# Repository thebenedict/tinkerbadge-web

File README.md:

# Tinker Badge Web Viewer

A static KiCad project viewer with an interactive 3D assembly, searchable schematics, PCB layers, and source documentation. Project metadata and native CAD exports drive the pages. Tinker Badge is the current integration target; Harvest remains a separate regression example.

## Run locally

Requires Node 18+ and Python 3. CAD exports use KiCad 10.0.8.

```sh
npm ci
npm run build
npm run preview
```

Open **http://127.0.0.1:4173**. The preview serves `dist/` on loopback. Use HTTP rather than opening HTML through `file://`.

The included `public/data/` snapshot can rebuild the interface without KiCad. Its manifest identifies the actual project and snapshot. `npm run dev` builds and starts the preview. After editing files, rebuild and refresh the browser.

## Export a project

```sh
npm run export:badge
npm run check
```

For Harvest:

```sh
npm run export:harvest
npm run check
```

For another configuration or source location:

```sh
python3 scripts/export_assets.py \
  --config config/badge.json \
  --source ../tinkerbadge-hardware \
  --kicad-cli /Applications/KiCad/KiCad.app/Contents/MacOS/kicad-cli
```

The exporter copies allowlisted native files, local libraries, and referenced models into a private working directory. It runs KiCad against those copies, checks source and dependency hashes again, and promotes the new manifest only after the export completes. Native downloads retain the original source bytes. Logs stay in `.work/`.

Export from a consistent CAD checkpoint. If a sheet, footprint, model, document, or dependency changes during export, the snapshot is rejected. The badge configuration also pins the approved board hash; update that pin only after reviewing a new hardware checkpoint. Before export, run the hardware repository’s `tools/refresh_publication.py` and commit the resulting snapshot. The web exporter verifies that its selected source files match one hardware commit, and that the manufacturing, electrical and enclosure evidence all match those files. It reads the hardware project without modifying it.

## Project metadata

`config/badge.json` and `config/harvest.json` use schema version 2. A project configuration names:

- The source directory, relative to this viewer project unless overridden with `--source`.
- The project name, description, revision, status, and maintained README.
- Explicit variant IDs and paths to the root schematic, PCB, and KiCad project.
- The native instance project name used by hierarchical schematics.
- Documents and CAD directories to include in the source bundle.
- Optional facts, named assembly accessories, and source-backed component-name inputs.

The schematic and PCB inputs are independent. A schematic-only project gets a schematic preview and no PCB tab. A board with an outline can have a 3D view before placement. Missing model geometry leaves the schematic, PCB layers, and available component metadata usable.

To adapt another KiCad project, add a configuration with its real filenames and metadata, export it, run the checks, and review the resulting pages. The current adapter targets KiCad 10's native file and export structures. Unfamiliar hierarchy or model conventions need validation and tests before release.

Interface copy lives in `config/presentation.json` and applies only to its matching `projectName`. It can override the landing product line, supply brief example interactions, and omit named README sections from the landing page. The full source README, its document page, and the native download remain unchanged.

## Views

- **Overview:** maintained README, source documents, assembly poster, optional interactive model, and downloads.
- **Schematic:** pan, zoom, fit, hierarchical sheet selection, project-wide name/reference/value search, source properties, and PDF/SVG/native downloads.
- **PCB:** all exported copper layers, fabrication and mask layers, mirrored back view, front/back presets, and name/reference/value/net search.

Each variant and view has a static URL. Sheet links use the full native sheet-instance identity. Searching for a component on another sheet opens that sheet and focuses its symbol. A component's 3D details link to the matching PCB reference and schematic sheet.

The model runtime, GLB, and component index load after **Explore in 3D**. Schematic and PCB drawings load on their own pages. All viewer assets use the same origin; no backend is required.

## Components and assembly accessories

Click a component to highlight it and read its descriptive name, reference, value, part number, supplier code, footprint, BOM inclusion, quantity, and nets. Datasheet links come from the source. The reference selector provides the same details without precise pointing. Parts without a separate model remain selectable in the list.

**Focus** moves the camera toward the selected model. **Clear** or Escape removes the selection. Dragging and multi-pointer gestures do not select a component. Visible PCB and accessory geometry blocks picking through it.

The badge's **Show display and battery** checkbox controls separate assembly objects. It starts off in 3D; enable it to show the source-derived assembly geometry. An explicit choice is retained for that model in the current tab, including retries and browser Back navigation. The display is a source-derived glass envelope with a proposed 4.5 mm underside clearance. The battery is a 35 × 55 × 7 mm size allowance; the pack, cable, and mounting are still open. These objects are excluded from the electrical BOM.

Accessory metadata names an exact native board-only footprint and source model. When KiCad omits the review WRL from GLB, the exporter can reconstruct its verified cuboids and calibrate placement against native component transforms on both board sides. Unsupported geometry or inconsistent anchors disables that fallback. The interactive viewer does not invent mounting hardware, cables, or flex routing.

## Identity and provenance

Each PCB record keeps its footprint UUID and native schematic instance path. The exporter resolves a root-relative path only against the known schematic root, then checks the reference. It compares values, footprints, BOM fields, and assembly flags. Unplaced symbols and board-only items remain explicit; conflicting properties are reported and details use the PCB values.

The GLB binder verifies KiCad's reference-named assembly parents and adds variant-qualified UUIDs in node extras. `components.json` records source hashes, model hash, metadata, and exact mesh ownership. Ambiguous identities stop binding. Missing bodies are recorded as missing rather than assigned to a nearby part.

For reviewed routing checkpoints, optional `routingReview` inputs identify the checkpoint manifest, native DRC report, exact remaining endpoints, and review document. The exporter binds them to the board hash and validates report counts and endpoint agreement. Their source hashes accompany the PCB-only progress note; inconsistent reports stop export.

The browser validates the index before enabling inspection. Picking follows UUID ancestry from actual mesh hits. The model optimizer merges compatible primitives within each mesh and verifies triangle attributes, winding, materials, names, transforms, and bounds. The original native GLB is included as a download.

Readable names come from the planning BOM's Description tables, joined through reviewed reference-to-BOM contracts and exact current part numbers. A unique part-number match is allowed only when it identifies one current reference. Shared parts do not inherit another circuit's role. Standard resistor, capacitor, and inductor names can use their embedded native library descriptions. Missing or ambiguous names keep the native value instead.

The same `displayName` and `displayNameSource` fields reach the 3D index, verified PCB records, and schematic symbols. Source paths, hashes, table rows, and association evidence remain available for audit. Names are searchable in both drawing views.

BOM quantity is the populated count of the exact part in the selected board snapshot. Historical BOM CSVs, stock, and prices are not used.

## Controls

**3D:** drag to orbit. Focus the canvas before scrolling to zoom. Keyboard arrows rotate, +/− zoom, and Home resets. On touch screens, use two fingers to orbit and zoom. Rendering runs when the view changes and pauses in background tabs.

**2D:** drag to pan, scroll or pinch to zoom. Keyboard arrows pan, +/− zoom, and Home/0 fit. Search results focus symbol or footprint origins.

On the PCB, **Back** mirrors the viewing direction. **Back set** selects the rear layers. These controls are independent.

## Verify changes

```sh
npm run check
```

This runs unit tests, builds the static pages, checks local links and artifact hashes, validates hierarchy and component identities, probes real model triangles, and checks that PCB layers share a coordinate system. Browser checks and remaining coverage are recorded in `QA.md`.

For an isolated fixture, set `VIEWER_PUBLIC` and `VIEWER_DIST` to separate directories inside this project. `VIEWER_PUBLIC` contains `data/manifest.json`; `VIEWER_DIST` is the generated site. Build, check, and preview scripts honor these paths. `PORT` changes the loopback preview port.

Read `docs/style_guide/writing.md` before changing copy. Use descriptive labels and omit decorative numbering. Native sheet names and source documents retain their maintained text.

## Deployment

`dist/` is the complete static site and uses relative URLs for subpath hosting. Deploy it as a unit only after checking its manifest and project identity. Content-hashed scripts, styles, and immutable snapshot assets can be cached independently of entry pages.

See [publishing setup](docs/publishing.md) for release checks and deployment configuration. Review third-party model licenses before public redistribution.

## Current limits

- PCB revision 0.3 has zero open connections or error-severity ERC/DRC findings in the bound publication evidence. The enclosure is an A2 fit prototype; battery, display, RF and physical qualification remain open.
- Component selection marks real model bodies; 2D reference markers mark symbol or footprint origins. Live cross-highlighting between separate open views is future work.
- The maintained README is rendered from its source, with configured landing-page omissions. Links outside the snapshot allowlist appear as dotted text.
- Arbitrary STEP assemblies, unusual nested model exports, and unsupported accessory meshes need adapter work and tests.
- Physical-phone performance, sustained memory use, Safari, and Firefox still need testing.

## Files

- `config/`: explicit project metadata and source allowlists
- `src/`: browser modules and styles
- `scripts/export_assets.py`: frozen snapshots and native KiCad exports
- `scripts/kicad_source.py`: source parsing, hierarchy, models, and metadata
- `scripts/component_names.py`: BOM and native-description names with provenance
- `scripts/presentation.mjs`: landing-page README filtering
- `scripts/interactions.mjs`: static example-interaction lists with decorative sketches
- `scripts/bind_components.mjs`: component and accessory bindings
- `scripts/optimize_glb.mjs`: checked per-mesh primitive consolidation
- `scripts/build.mjs`: static pages and browser bundles
- `scripts/check.mjs`: artifact and integration checks
- `scripts/qa-serve.mjs`: local error and loading fixtures
- `tests/`: JavaScript and Python regression tests
- `public/data/`: immutable exports and active manifest
- `dist/`: generated static site
- `.work/`: copied inputs, export logs, and local fixtures

See `web_viewer.md` for the longer-term specification.

## Feature callouts

The badge front page starts with Front, Components, and Back KiCad renders and labeled hardware features. Desktop shows all leader lines. On phones, every label stays visible and selecting one shows its leader line. Keyboard users can select a view and move through the labels. The 3D model still loads only after **Explore in 3D**.

Feature copy and one representative reference per feature live in `config/features/badge.json`. Each label has a single leader. Anchors come from the snapshot’s native PCB coordinates, including the mirrored back view. `public/features/badge/renders.json` records the source snapshot, board hash, render hashes, and calibrated pixel transforms. A build refuses stale renders, missing or wrong-side references, unmarked board-only reservations, or changed image dimensions.

The labels describe proposed interactions. The Components render hides the display to expose front electronics. The Back render includes the battery allowance and the routed rear NFC coil. The SAO socket is on the front. NFC tuning remains open. Accessory leaders use their native assembly positions. These presentation exports do not change the source board or interactive assembly.

To regenerate these three presentation images from the reviewed snapshot, run `python3 scripts/render_feature_views.py`, then `npm run check`. The render recipe is intentionally pinned to the reviewed badge source; review its snapshot and source-hash binding when replacing the hardware layout. Calibration uses six native mounting holes. An independent shoulder transparency check verifies front/back orientation; the full outline stays in frame.

## Licensing

- Original viewer software and tools: **Apache-2.0**.
- Original documentation and artwork: **CC-BY-4.0**.
- Original Tinker Badge hardware in snapshots: **CERN-OHL-P-2.0**.

See [the licensing map](LICENSE.md), [full license texts](LICENSES/README.md), and [third-party notices](docs/THIRD_PARTY_NOTICES.md). Generated assets retain their source licenses; imported projects and dependencies retain their own terms.

## Enclosure viewer

The [enclosure exploration guide](docs/enclosure-viewer.md) describes assembly views, CAD refresh, and validation.

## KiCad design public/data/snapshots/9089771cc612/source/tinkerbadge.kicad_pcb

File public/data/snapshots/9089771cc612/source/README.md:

# Tinker Badge hardware

Open **tinkerbadge.kicad_pro** in KiCad 10. The root schematic links to power, processor, display, lighting and peripheral sheets.

- [Specification](docs/spec.md)
- [Current schematic decisions and remaining gates](docs/design/implementation_status.md)
- [Reviewed physical-pin assignments](docs/pinouts.md)
- [Verification results](docs/design/verification.md)
- [Planning BOM and source history](docs/AI_Tinkerers_Badge_Design_BOM_Draft_2026-11-09.md)

The first prototype uses a single nominal 3.3 V rail for logic and the eight RGB LEDs. Regulator tolerance can fall below the LED datasheet minimum, so startup, low-battery, radio and full-white load-step tests are required.

This is a development schematic. The battery interface is two-wire, with an optional unpopulated thermistor connection. **Onboard charging is disabled in the initial variant.** Several connector/footprint, charging, thermal and prototype checks remain before board release.

## Repeat the electrical check

Export the complete root schematic netlist using KiCad CLI or the installed Konnect MCP, then run:

```
python3 tools/check_schematic_contracts.py path/to/export.net --output path/to/endpoint-result.json
python3 tools/check_schematic_properties.py path/to/export.net --output path/to/property-result.json
python3 tools/test_contract_checker.py
python3 tools/test_property_checker.py
python3 tools/test_alps_buttons.py
```

The checker compares every physical pin and intentional NC with the separately maintained reviewed block contracts. The separate property checker covers explicitly declared values, part numbers, ratings, population and library associations. Run root ERC and inspect fresh sheet renders as well. Current outputs are in `exports/`, with a six-page PDF and a pinned verification manifest. The one-time capture scripts are not idempotent rebuild commands; rerunning them blindly can duplicate objects. Initial electrical capture used Konnect MCP. The user-approved [outlined-block revision](docs/design/outlined_blocks_review.md) uses bounded native edits, independent visual review and complete before/after exported-netlist comparison.

## Licensing

- Original hardware and mechanical designs: **CERN-OHL-P-2.0**.
- Original software, tools and firmware: **Apache-2.0**.
- Original documentation and artwork: **CC-BY-4.0**.

See [the licensing map](LICENSE.md) and [full license texts](LICENSES/README.md). Generated exports retain their source licenses. [Third-party notices](docs/THIRD_PARTY_NOTICES.md) cover KiCad libraries and manufacturer material.

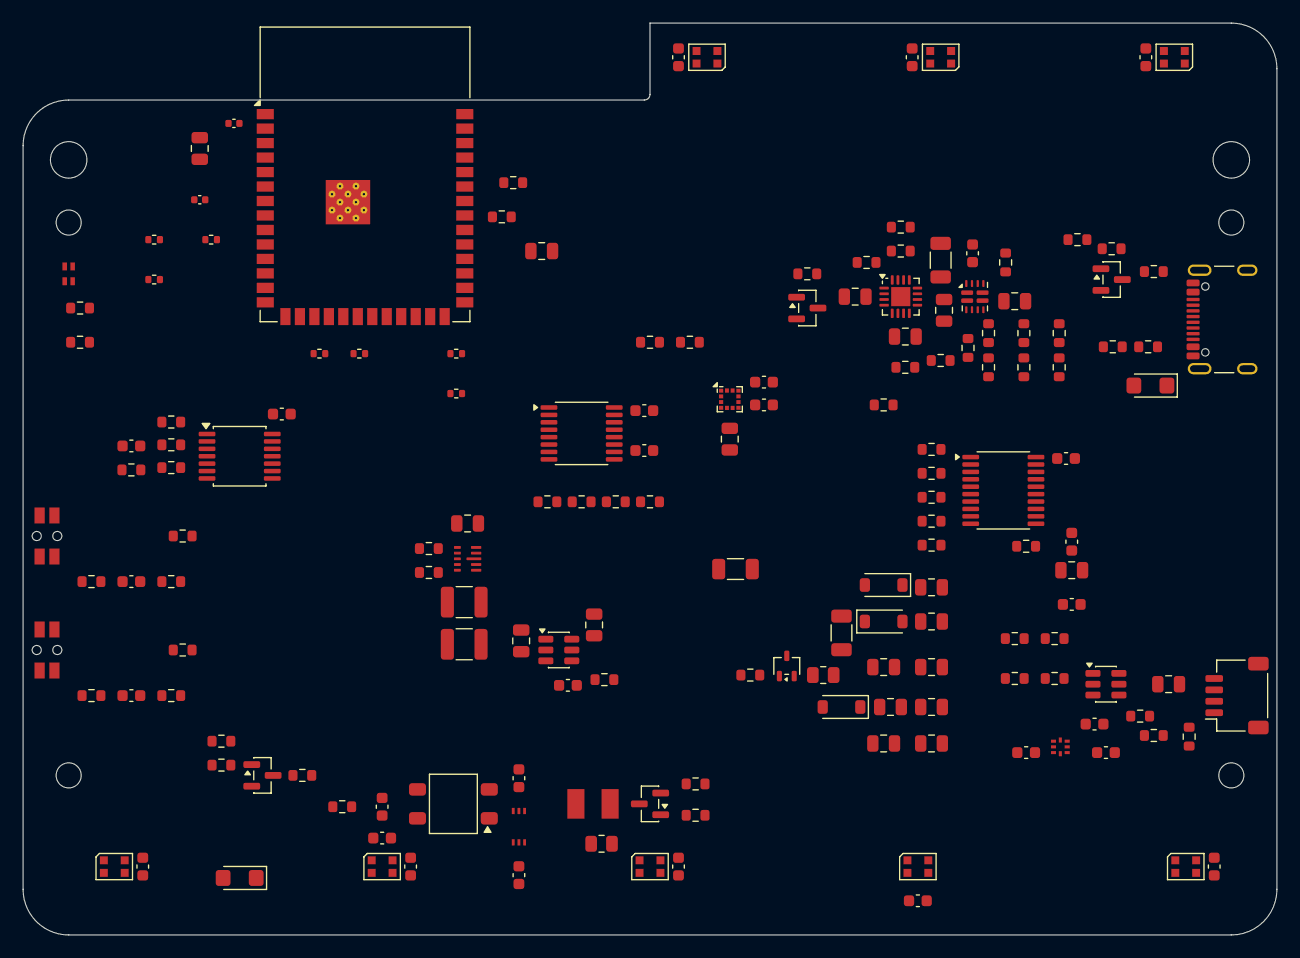
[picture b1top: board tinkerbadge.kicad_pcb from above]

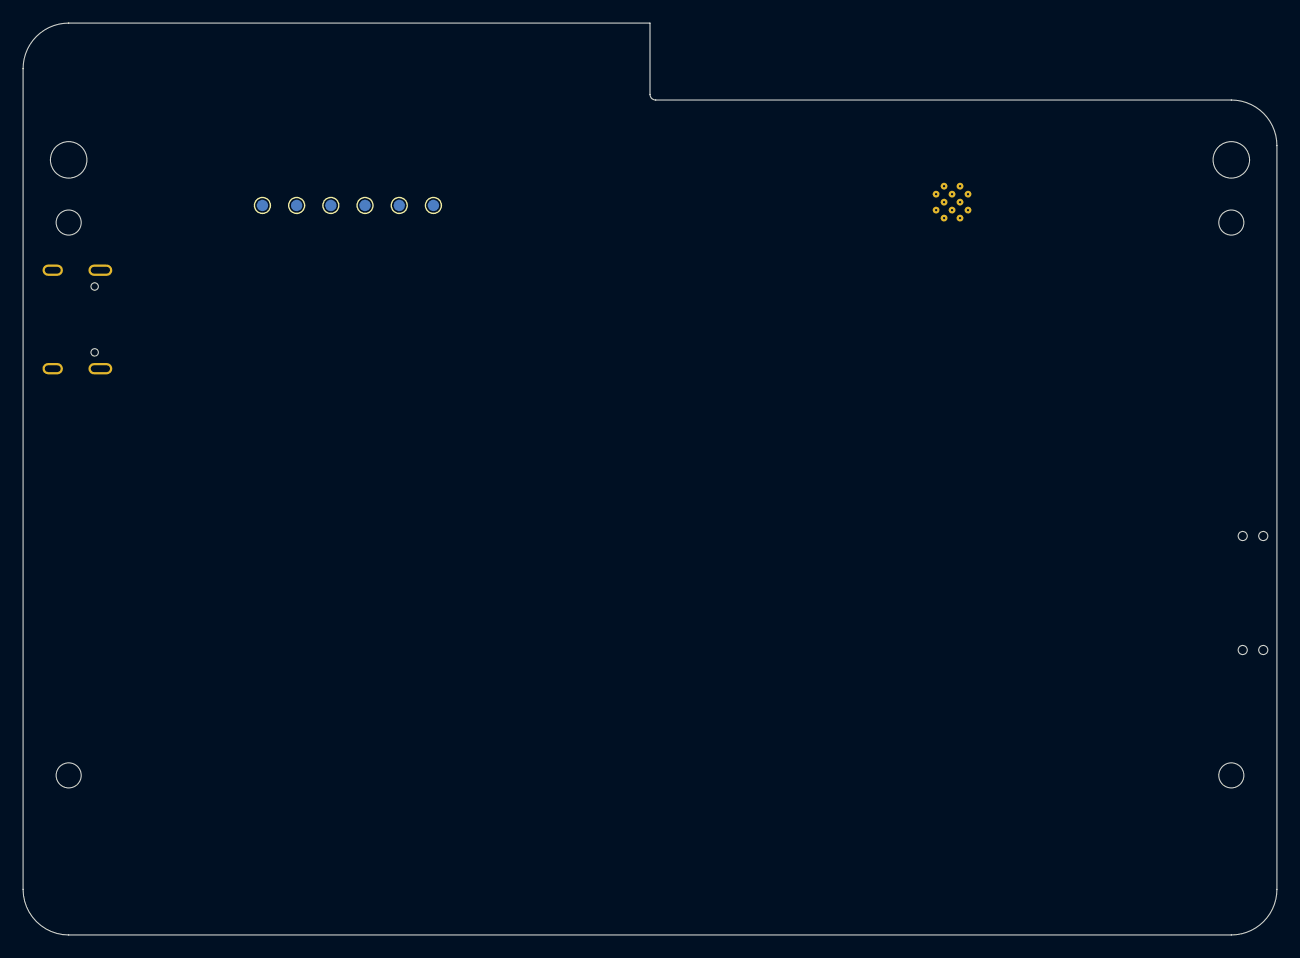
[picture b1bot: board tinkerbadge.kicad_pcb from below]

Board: 4 copper layers, 110.0 x 80.0 mm, 186 parts (9 on the bottom side), 95 nets, no tracks yet.

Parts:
C101, C102: 1uF 25V X7R; C_0805_2012Metric
C103: 4.7uF 25V X7R; C_1206_3216Metric
C104: 100nF 16V X7R; C_0603_1608Metric
C105, C106, C107: 10uF 10V X7R; C_0805_2012Metric
C108, C109: 22uF 10V X7R; C_1210_3225Metric
C112: 1uF 6.3V X7R; C_0805_2012Metric
C113: 1nF 16V C0G; C_0603_1608Metric
C114: 10uF 6.3V X7R; C_0805_2012Metric
C115: 100nF 6.3V X7R; C_0603_1608Metric
C116: 10nF 6.3V X7R; C_0603_1608Metric
C201: 22uF 10V X5R; C_0805_2012Metric
C202: 100nF 16V X7R; C_0402_1005Metric
C203: 1uF 10V X7R; C_0402_1005Metric
C301, C302: 4.7u / 50V; C_1206_3216Metric
C303, C312, C401, C402, C403, C404, C405, C406, C407, C408, C411, C412, C501, C502, C503, C504, C506, C510, C514: 100n / 10V; C_0603_1608Metric
C304: 1u / 10V; C_0805_2012Metric
C305, C311: 1u / 25V; C_0805_2012Metric
C306, C307, C308, C309, C310: 1u / 50V; C_0805_2012Metric
C409: 22u / 10V; C_0805_2012Metric
C505, C512, C513: 10u / 10V; C_0805_2012Metric
C507, C508: TUNE / DNP; C_0603_1608Metric
C509: 4.7u / 10V; C_0603_1608Metric
C511, C515: 1u / 10V; C_0603_1608Metric
D101, D102: SMF6.0A
D301, D302, D303: MBR0530T1G; D_SOD-123
D401, D402, D403, D404, D405, D406, D407, D408: WS2812C-2020-V6; WS2812C-2020-V6_Reviewed
D409: HSMF-C165
D501: IR67-21C/TR8; IR67-21C_TR8
H1, H2, H3, H4: PROVISIONAL; MountingHole_2.2mm_M2
H5, H6: REVIEW ENVELOPE ONLY; Review_Cord_Hole_3p2
J101: USB4105-GF-A; USB4105-GF-A_ProjectShells
J501: SM04B-SRSS-TB(LF)(SN); JST_SH_SM04B_ProjectTabs
MECH_BATTERY: REVIEW ONLY; Review_Battery_Allowance
MECH_NFC: REVIEW ENVELOPE ONLY; Review_NFC_18x13
MECH_PANEL: REVIEW ENVELOPE ONLY; Review_Panel_Raised_4p5
Q101, Q102, Q103, Q501: AO3400A; SOT-23
Q301: Si1308EDL-T1-GE3; SOT-323_SC-70
R101, R102: 5.1k 1%; R_0603_1608Metric
R103, R105: 44.2k 0.1%; R_0603_1608Metric
R104, R106, R108, R118: 10.0k 0.1%; R_0603_1608Metric
R107: 31.6k 0.1%; R_0603_1608Metric
R109: 80.6k 1%; R_0603_1608Metric
R110: 10k 1%; R_0603_1608Metric
R111, R115, R116, R121, R123, R124, R126: 100k 1%; R_0603_1608Metric
R112: 4.32k 1%; R_0603_1608Metric
R113: 3.32k 1%; R_0603_1608Metric
R114: 47.5k 1%; R_0603_1608Metric
R117: 56.0k 0.1%; R_0603_1608Metric
R119: 1k 1%; R_0603_1608Metric
R120: 0; R_0603_1608Metric
R122, R125: 470k 1%; R_0603_1608Metric
R127, R128, R129: 100k 0.1%; R_0603_1608Metric
R130: 10k 0.1%; R_0603_1608Metric
R201, R202, R203, R204: 10k 1%; R_0402_1005Metric
R205, R206: 22R 1%; R_0402_1005Metric
R207: 100k 1%; R_0402_1005Metric
R301: 0.47 / 0.25W; R_0805_2012Metric
R302, R503: 10k; R_0603_1608Metric
R303, R304, R305, R306, R307, R308, R402, R405, R406, R412, R414, R506, R509, R510, R511, R514, R515, R516, R517: 100k; R_0603_1608Metric
R401, R411, R413: 330; R_0603_1608Metric
R403, R404: 2.2k; R_0603_1608Metric
R501, R502, R512, R513: 4.7k; R_0603_1608Metric
R504: 100; R_0805_2012Metric
R505, R507: 100; R_0603_1608Metric
R508: 210k; R_0603_1608Metric
RES_J102: REVIEW ONLY; Review_Battery_Connector
RES_J103: REVIEW ONLY; Review_Dock_Contacts
RES_J301: REVIEW ONLY; Review_Flex_Mating
RES_J502: REVIEW ENVELOPE ONLY; Review_SAO_Front_Tail_Reserve
RES_L101: REVIEW ONLY; Review_Inductor_6x6
RES_L301: REVIEW ONLY; Review_Inductor_5x5
RES_U105: REVIEW ONLY; Review_ESD_Package
SW401, SW402: SKSCLBE010
TP201: MCU_EN; TestPoint_Pad_D1.0mm
TP202: BOOT_N; TestPoint_Pad_D1.0mm
TP203: +3V3; TestPoint_Pad_D1.0mm
TP204: GND; TestPoint_Pad_D1.0mm
TP205: UART_TX; TestPoint_Pad_D1.0mm
TP206: UART_RX; TestPoint_Pad_D1.0mm
U101: TPS2121RUXR; TPS2121RUXR_Reviewed
U102: BQ24074RGTR; BQ24074RGTR_Reviewed
U103: TPS63802DLAR; TPS63802_DLA0010A_Reviewed
U104: TPS22918DBVR; SOT-23-6
U107: TMUX1511PWR; TSSOP-14_4.4x5mm_P0.65mm
U201: ESP32-S3-WROOM-1-N16R8; ESP32-S3-WROOM-1
U301: SN74LVC541APWR; TSSOP-20_4.4x6.5mm_P0.65mm
U501: BH1730FVC; BH1730FVC_WSOF6
U502: LIS2DW12TR; LGA-12_2x2mm_P0.5mm
U503: NT3H2111W0FHKH; NT3H2111W0FHKH_XQFN8
U504: IRM-H638T/TR2; IRM-H638T_Reviewed
U505: TPS2553DBVR; SOT-23-6
U506: TCA9534PWR; TSSOP-16_4.4x5mm_P0.65mm

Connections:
+3V3: C108.1, C109.1, C112.1, C115.1, C201.1, C202.1, C401.1, C402.1, C403.1, C404.1, C405.1, C406.1, C407.1, C408.1, C409.1, C501.1, C502.1, C503.1, C504.1, C505.1, C506.1, C511.1, C512.1, C514.1, C515.1, D401.4, D402.4, D403.4, D404.4, D405.4, D406.4, D407.4, D408.4, R115.1, R116.1, R117.1, R123.1, R126.1, R201.1, R202.1, R305.2, R412.1, R414.1, R501.1, R502.1, R503.1, R504.1, R510.1, TP203.1, U103.6, U104.1, U107.1, U107.14, U201.2, U501.1, U501.5, U502.2, U502.3, U502.9, U502.10, U503.6, U505.1, U506.16
+3V3_EPD: C114.1, C301.1, C303.1, C312.1, R119.1, U104.6, U301.20
/01 POWER + CHARGING/BAT_DIV_PRE: C116.1, R127.2, R128.1, U107.2
/01 POWER + CHARGING/BAT_SENSE_ISOLATED: R130.1, U107.3
/01 POWER + CHARGING/CHARGER_EN1: Q103.3, R111.2, U102.6
/01 POWER + CHARGING/CHARGER_ILIM: R112.1, U102.12
/01 POWER + CHARGING/CHARGER_ISET: R113.1, U102.16
/01 POWER + CHARGING/CHARGER_TMR: R114.1, U102.14
/01 POWER + CHARGING/CHARGE_DISABLE: R120.2, U102.4
/01 POWER + CHARGING/DOCK_PRESENT_GATE: Q102.1, R124.2, R125.1
/01 POWER + CHARGING/EPD_CT: C113.1, U104.4
/01 POWER + CHARGING/EPD_QOD: R119.2, U104.5
/01 POWER + CHARGING/MUX_ILM: R109.1, U101.10
/01 POWER + CHARGING/MUX_OV_DOCK: R105.2, R106.1, U101.4
/01 POWER + CHARGING/MUX_OV_USB: R103.2, R104.1, U101.5
/01 POWER + CHARGING/MUX_PRIORITY_USB: R107.2, R108.1, U101.6
/01 POWER + CHARGING/MUX_SS: C104.1, U101.11
/01 POWER + CHARGING/MUX_USB_SELECTED: Q103.1, R110.2, U101.9
/01 POWER + CHARGING/PRIMARY_FB: R117.2, R118.1, U103.4
/01 POWER + CHARGING/USB_CC1: J101.A5, R101.1
/01 POWER + CHARGING/USB_CC2: J101.B5, R102.1
/01 POWER + CHARGING/USB_PRESENT_GATE: Q101.1, R121.2, R122.1
/01 POWER + CHARGING/VBAT_PROTECTED: C106.1, R127.1, U102.2, U102.3
/01 POWER + CHARGING/VEXT_5V: C103.1, U101.1, U101.8, U102.13
/01 POWER + CHARGING/VSYS: C105.1, C107.1, R110.1, R111.1, R120.1, U102.10, U102.11, U103.1, U103.10
/02 PROCESSOR + RECOVERY/BOOT_N: R202.2, TP202.1, U201.27
/02 PROCESSOR + RECOVERY/MCU_EN: C203.1, R201.2, TP201.1, U201.3
/02 PROCESSOR + RECOVERY/MCU_USB_DM: R205.2, U201.13
/02 PROCESSOR + RECOVERY/MCU_USB_DP: R206.2, U201.14
/02 PROCESSOR + RECOVERY/STRAP45: R203.1, U201.26
/02 PROCESSOR + RECOVERY/STRAP46: R204.1, U201.16
/02 PROCESSOR + RECOVERY/UART_RX: TP206.1, U201.36
/02 PROCESSOR + RECOVERY/UART_TX: TP205.1, U201.37
/03 E-PAPER DISPLAY/EPD_GDR: Q301.1, R302.1
/03 E-PAPER DISPLAY/EPD_PUMP: C302.2, D301.2, D302.1
/03 E-PAPER DISPLAY/EPD_RESE: Q301.2, R301.1
/03 E-PAPER DISPLAY/EPD_SW: C302.1, D303.2, Q301.3
/03 E-PAPER DISPLAY/EPD_VGH: C307.1, D303.1
/03 E-PAPER DISPLAY/EPD_VGL: C309.1, D302.2
/04 LIGHTING + BUTTONS/BTN_A_SW_N: R411.1, SW401.1, SW401.2
/04 LIGHTING + BUTTONS/BTN_B_SW_N: R413.1, SW402.1, SW402.2
/04 LIGHTING + BUTTONS/PWR_GREEN_A: D409.1, R403.2
/04 LIGHTING + BUTTONS/PWR_RED_A: D409.2, R404.2
/04 LIGHTING + BUTTONS/RGB_DIN: D401.3, R401.2, R402.1
/04 LIGHTING + BUTTONS/RGB_LINK_1: D401.1, D402.3
/04 LIGHTING + BUTTONS/RGB_LINK_2: D402.1, D403.3
/04 LIGHTING + BUTTONS/RGB_LINK_3: D403.1, D404.3
/04 LIGHTING + BUTTONS/RGB_LINK_4: D404.1, D405.3
/04 LIGHTING + BUTTONS/RGB_LINK_5: D405.1, D406.3
/04 LIGHTING + BUTTONS/RGB_LINK_6: D406.1, D407.3
/04 LIGHTING + BUTTONS/RGB_LINK_7: D407.1, D408.3
/05 SENSORS + EXPANSION/ACC_3V3: C513.1, J501.2, R507.1, R511.1, R512.1, R513.1, U505.6
/05 SENSORS + EXPANSION/ACC_EN: R509.1, U505.3, U506.6
/05 SENSORS + EXPANSION/ACC_FAULT_N: R510.2, U505.4, U506.7
/05 SENSORS + EXPANSION/ACC_ILIM: R508.1, U505.5
/05 SENSORS + EXPANSION/EXP_UNUSED_P4: R514.1, U506.9
/05 SENSORS + EXPANSION/EXP_UNUSED_P5: R515.1, U506.10
/05 SENSORS + EXPANSION/EXP_UNUSED_P6: R516.1, U506.11
/05 SENSORS + EXPANSION/EXP_UNUSED_P7: R517.1, U506.12
/05 SENSORS + EXPANSION/IR_GATE: Q501.1, R505.2, R506.1
/05 SENSORS + EXPANSION/IR_LED_A: D501.1, R504.2
/05 SENSORS + EXPANSION/IR_LED_K: D501.2, Q501.3
/05 SENSORS + EXPANSION/IR_RX_3V3: C509.1, C510.1, R507.2, U504.4
/05 SENSORS + EXPANSION/NFC_LA: C507.1, C508.1, U503.1
/05 SENSORS + EXPANSION/NFC_LB: C507.2, C508.2, U503.8
BAT_ADC: R129.1, R130.2, U201.39
BTN_A_N: C411.1, R411.2, R412.2, U201.38
BTN_B_N: C412.1, R413.2, R414.2, U201.4
CHARGER_CHG_N: R116.2, U102.9, U506.4
CHARGER_PGOOD_N: R115.2, U102.7, U506.5
DOCK_5V: C102.1, D102.1, R105.1, R124.1, U101.2
DOCK_PRESENT_N: Q102.3, R126.2, U201.6
EPD_BUSY: R308.1, U201.8
EPD_CS_N: R305.1, U201.18, U301.4
EPD_DC: R306.1, U201.21, U301.5
EPD_EN: R207.1, U104.3, U201.33
EPD_MOSI: R303.1, U201.19, U301.2
EPD_RST_N: R307.1, U201.22, U301.6
EPD_SCK: R304.1, U201.20, U301.3
EXT_SCL: J501.4, R513.2, U201.34
EXT_SDA: J501.3, R512.2, U201.9
GND: C101.2, C102.2, C103.2, C104.2, C105.2, C106.2, C107.2, C108.2, C109.2, C112.2, C113.2, C114.2, C115.2, C116.2, C201.2, C202.2, C203.2, C301.2, C303.2, C304.2, C305.2, C306.2, C307.2, C308.2, C309.2, C310.2, C311.2, C312.2, C401.2, C402.2, C403.2, C404.2, C405.2, C406.2, C407.2, C408.2, C409.2, C411.2, C412.2, C501.2, C502.2, C503.2, C504.2, C505.2, C506.2, C509.2, C510.2, C511.2, C512.2, C513.2, C514.2, C515.2, D101.2, D102.2, D301.1, D401.2, D402.2, D403.2, D404.2, D405.2, D406.2, D407.2, D408.2, D409.3, D409.4, J101.A1, J101.A12, J101.B1, J101.B12, J101.SH, J501.1, Q101.2, Q102.2, Q103.2, Q501.2, R101.2, R102.2, R104.2, R106.2, R108.2, R109.2, R112.2, R113.2, R114.2, R118.2, R122.2, R125.2, R128.2, R129.2, R203.2, R204.2, R207.2, R301.2, R302.2, R303.2, R304.2, R306.2, R307.2, R308.2, R402.2, R405.2, R406.2, R506.2, R508.2, R509.2, R511.2, R514.2, R515.2, R516.2, R517.2, SW401.3, SW401.4, SW402.3, SW402.4, TP204.1, U101.3, U101.12, U102.5, U102.8, U102.17, U103.2, U103.3, U103.8, U104.2, U107.4, U107.7, U107.10, U107.13, U201.1, U201.40, U201.41, U301.1, U301.7, U301.8, U301.9, U301.10, U301.19, U501.3, U502.5, U502.6, U502.7, U502.8, U503.2, U504.1, U504.2, U505.2, U506.1, U506.2, U506.3, U506.8
I2C_SCL: R502.2, U201.17, U501.6, U502.1, U503.3, U506.14
I2C_SDA: R501.2, U201.12, U501.4, U502.4, U503.5, U506.15
IR_RX_N: U201.11, U504.3
IR_TX: R505.1, U201.10
MOTION_INT1: U201.7, U502.12
NFC_FD_N: R503.2, U201.25, U503.4
PWR_LED_G: R403.1, R405.1, U201.31
PWR_LED_R: R404.1, R406.1, U201.32
RGB_DATA: R401.1, U201.23
USB_DM: J101.A7, J101.B7, R205.1
USB_DP: J101.A6, J101.B6, R206.1
USB_PRESENT_N: Q101.3, R123.2, U201.5
USB_VBUS: C101.1, D101.1, J101.A4, J101.A9, J101.B4, J101.B9, R103.1, R107.1, R121.1, U101.7
